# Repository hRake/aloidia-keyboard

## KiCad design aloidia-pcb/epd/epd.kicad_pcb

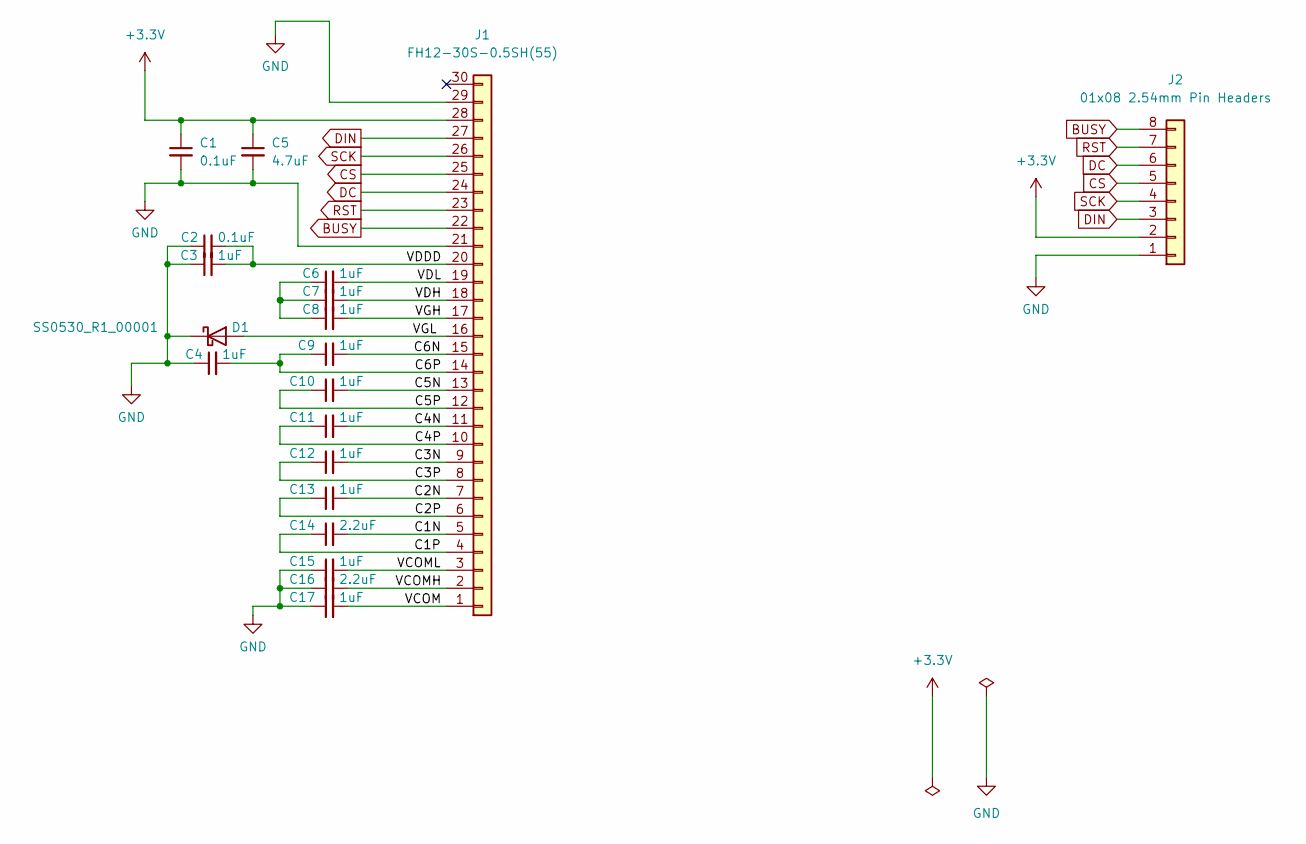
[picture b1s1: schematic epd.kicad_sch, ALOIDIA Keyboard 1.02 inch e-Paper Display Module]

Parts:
C1, C2: 0.1uF; C_0603_1608Metric
C3, C4, C6, C7, C8, C9, C10, C11, C12, C13, C15, C17: 1uF; C_0603_1608Metric
C5: 4.7uF; C_0603_1608Metric
C14, C16: 2.2uF; C_0603_1608Metric
D1: SS0530_R1_00001; D_SOD-123; Mouser ref 241-SS0530_R1_00001
J1: FH12-30S-0.5SH(55); JUSHUO AFC24-S30FIC-00; Mouser ref 798-FH12-30S-0.5SH55
J2: 01x08 2.54mm Pin Headers; PinHeader_1x08_P2.54mm_Vertical

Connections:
+3.3V: C1.1, C5.1, J1.28, J2.2
/C1N: C14.2, J1.5
/C1P: C14.1, J1.4
/C2N: C13.2, J1.7
/C2P: C13.1, J1.6
/C3N: C12.2, J1.9
/C3P: C12.1, J1.8
/C4N: C11.2, J1.11
/C4P: C11.1, J1.10
/C5N: C10.2, J1.13
/C5P: C10.1, J1.12
/C6N: C9.2, J1.15
/C6P: C4.2, C9.1, J1.14
/VCOM: C17.2, J1.1
/VCOMH: C16.2, J1.2
/VCOML: C15.2, J1.3
/VDDD: C2.2, C3.2, J1.20
/VDH: C7.2, J1.18
/VDL: C6.2, J1.19
/VGH: C8.2, J1.17
/VGL: D1.2 (A), J1.16
BUSY: J1.22, J2.8
CS: J1.25, J2.5
DC: J1.24, J2.6
DIN: J1.27, J2.3
GND: C1.2, C2.1, C3.1, C4.1, C5.2, C15.1, C16.1, C17.1, D1.1 (K), J1.21, J1.29, J2.1
unnamed: C6.1, C7.1, C8.1
RST: J1.23, J2.7
SCK: J1.26, J2.4

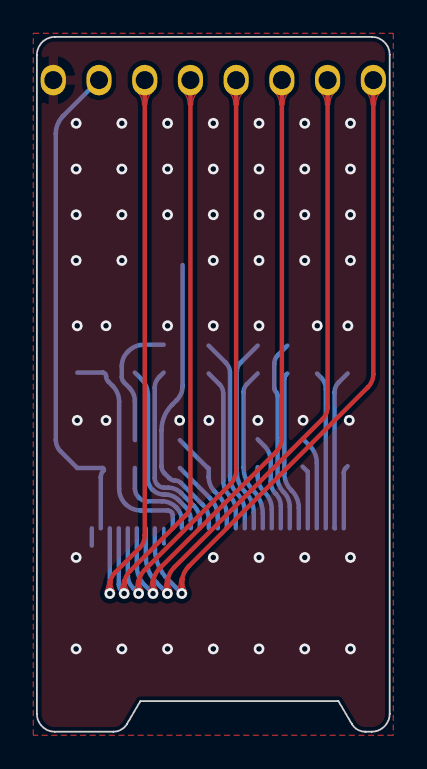
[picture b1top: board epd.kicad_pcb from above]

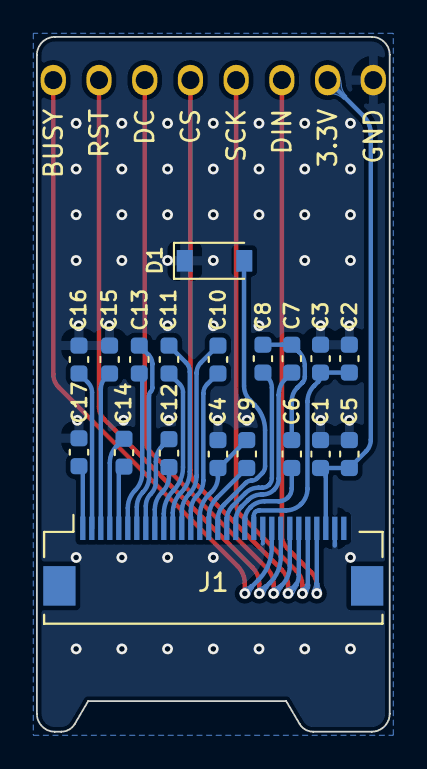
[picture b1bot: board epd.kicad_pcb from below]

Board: 2 copper layers, 19.6 x 38.6 mm, 20 parts (20 on the bottom side), 29 nets.

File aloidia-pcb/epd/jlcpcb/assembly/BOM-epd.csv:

Comment,Designator,Footprint,LCSC
0.1uF,"C1,C2",C_0603_1608Metric,C14663
1uF,"C10,C11,C12,C13,C15,C17,C3,C4,C6,C7,C8,C9",C_0603_1608Metric,C15849
4.7uF,C5,C_0603_1608Metric,C19666
2.2uF,"C14,C16",C_0603_1608Metric,C23630
FH12-30S-0.5SH(55),J1,JUSHUO AFC24-S30FIC-00,C262294
SS0530_R1_00001,D1,D_SOD-123,C8598

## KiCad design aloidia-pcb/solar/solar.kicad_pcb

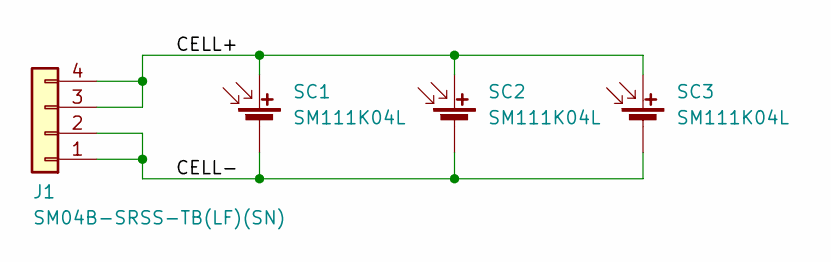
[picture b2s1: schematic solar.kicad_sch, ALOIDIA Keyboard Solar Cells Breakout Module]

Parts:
J1: SM04B-SRSS-TB(LF)(SN); JST_SH_SM04B-SRSS-TB_1x04-1MP_P1.00mm_Horizontal
SC1, SC2, SC3: SM111K04L; Digikey ref SM111K04L-ND

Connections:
/CELL+: J1.3, J1.4, SC1.1 (+), SC2.1 (+), SC3.1 (+)
/CELL-: J1.1, J1.2, SC1.2 (-), SC2.2 (-), SC3.2 (-)

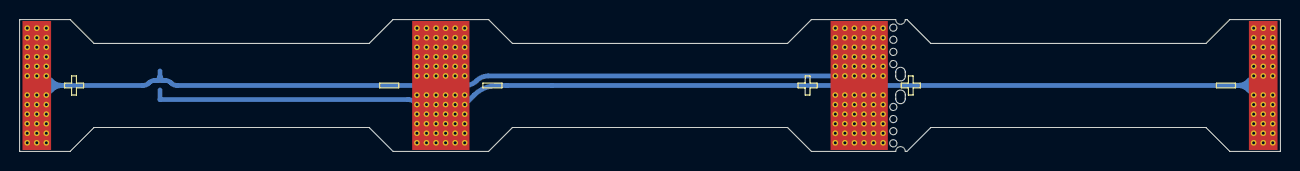
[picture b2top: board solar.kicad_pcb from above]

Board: 2 copper layers, 132.0 x 13.8 mm, 4 parts (1 on the bottom side), 2 nets.

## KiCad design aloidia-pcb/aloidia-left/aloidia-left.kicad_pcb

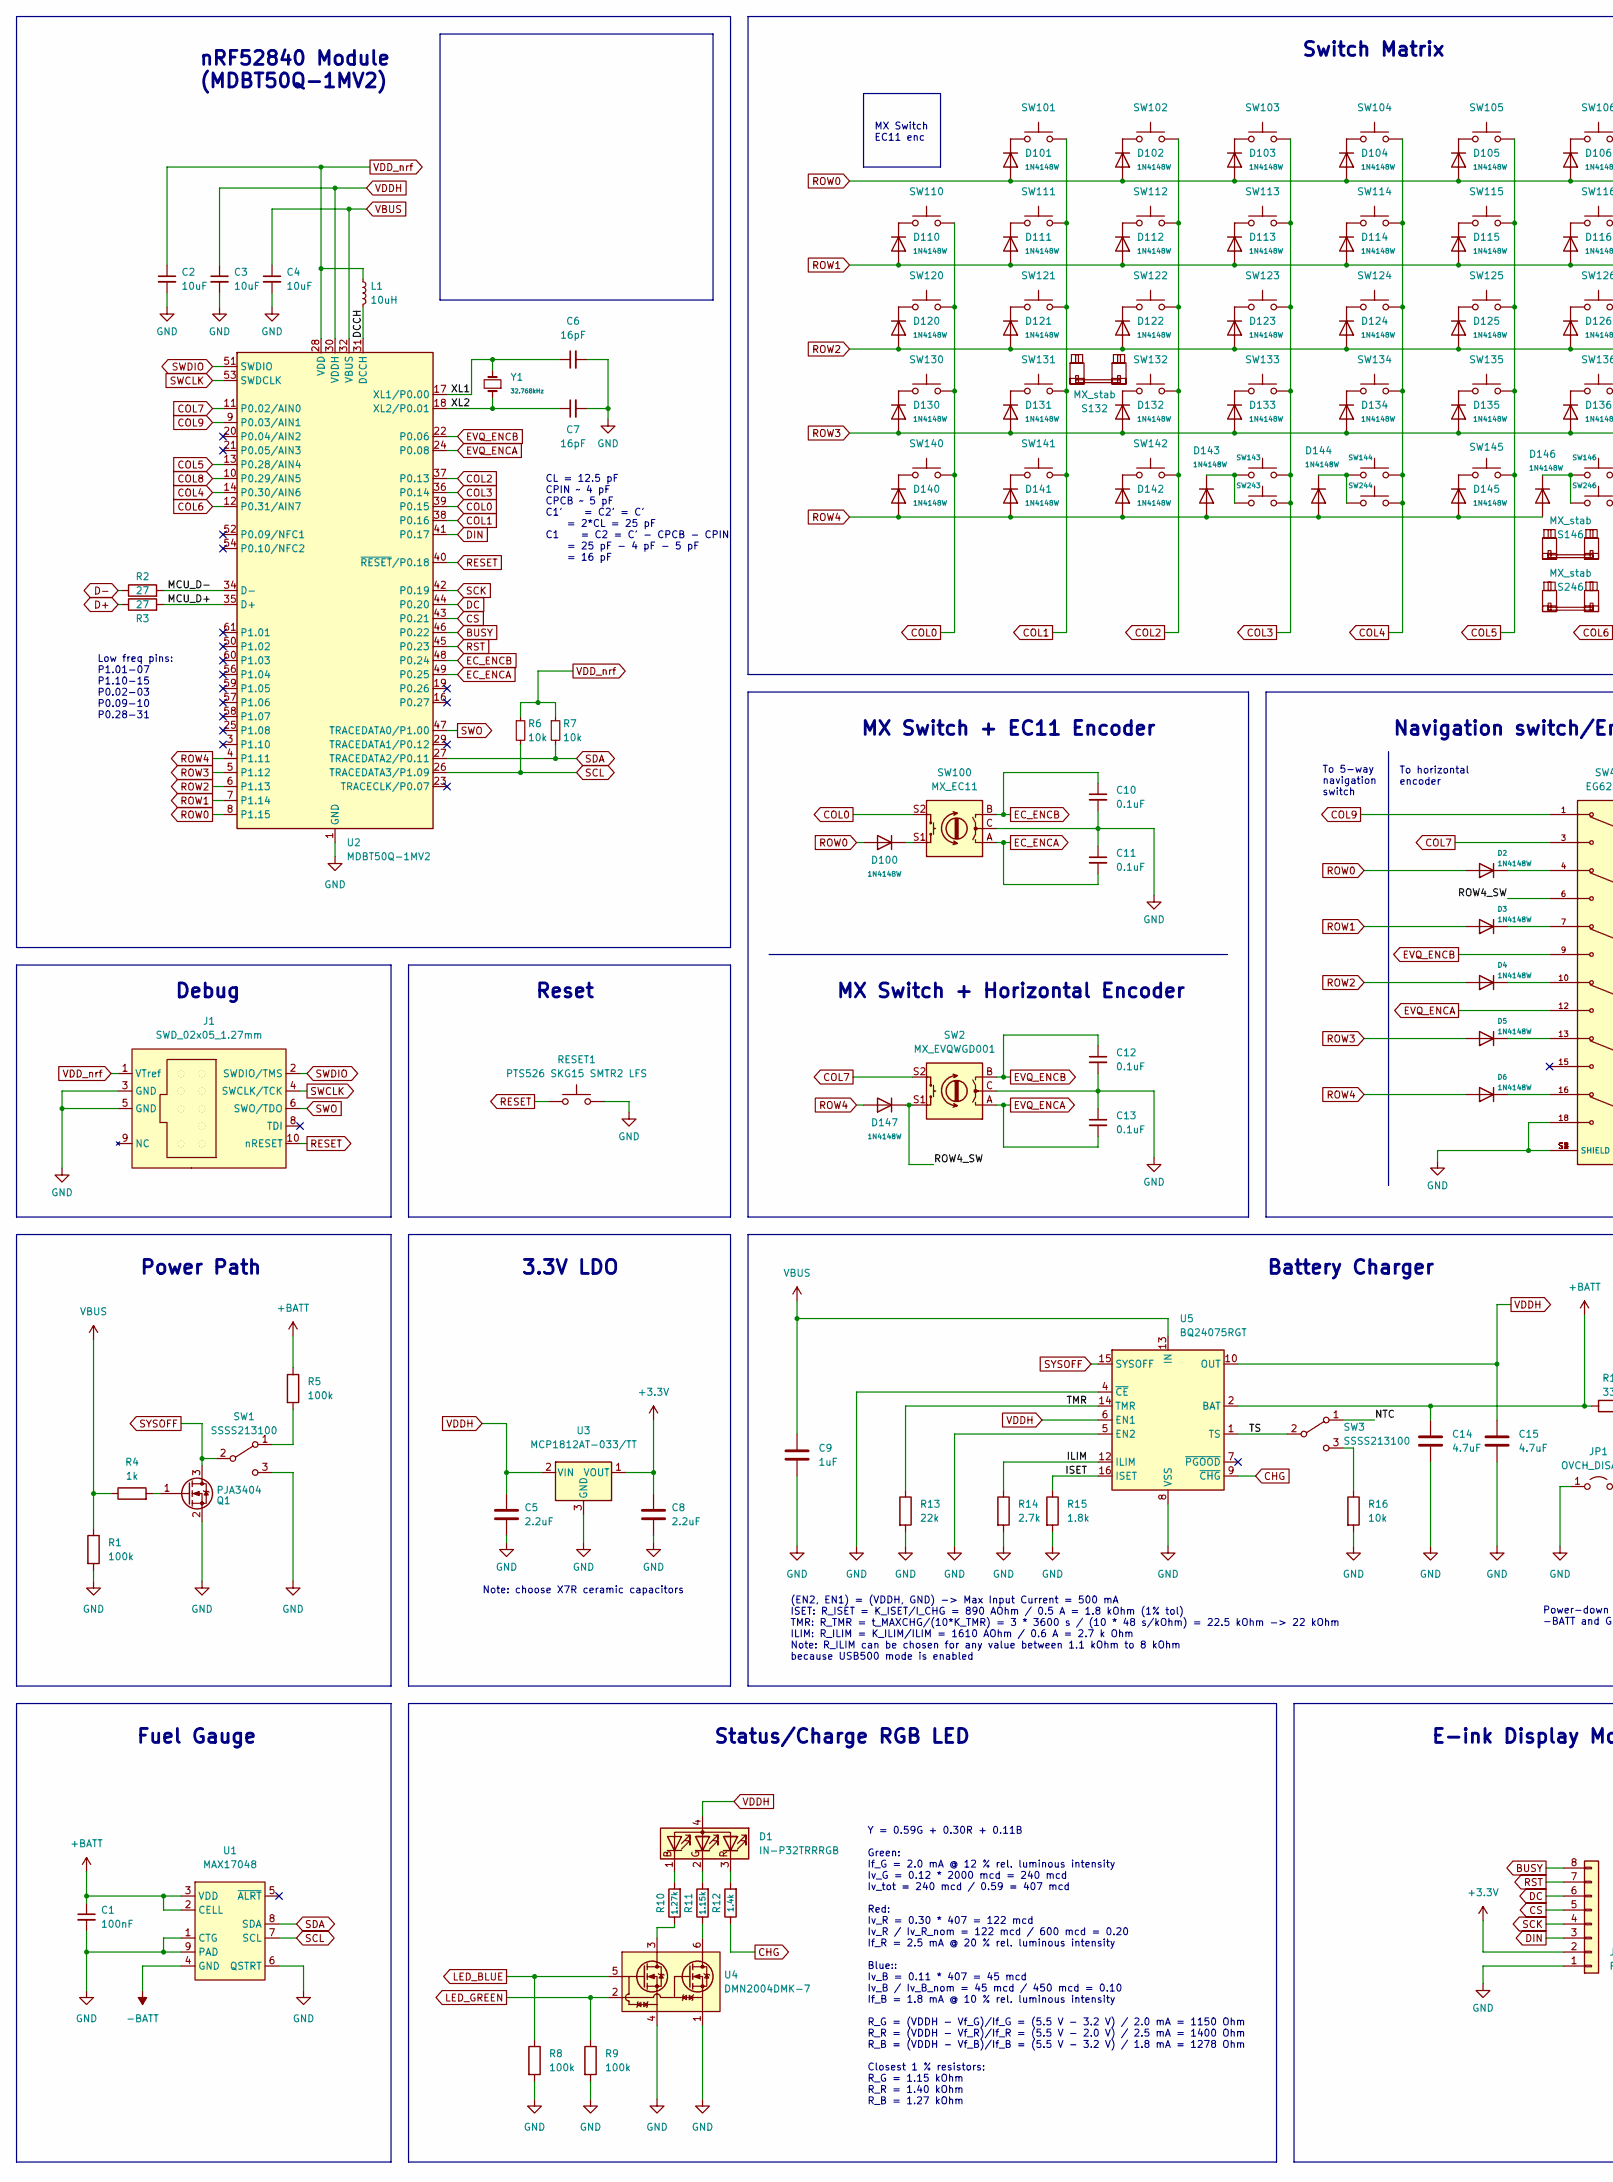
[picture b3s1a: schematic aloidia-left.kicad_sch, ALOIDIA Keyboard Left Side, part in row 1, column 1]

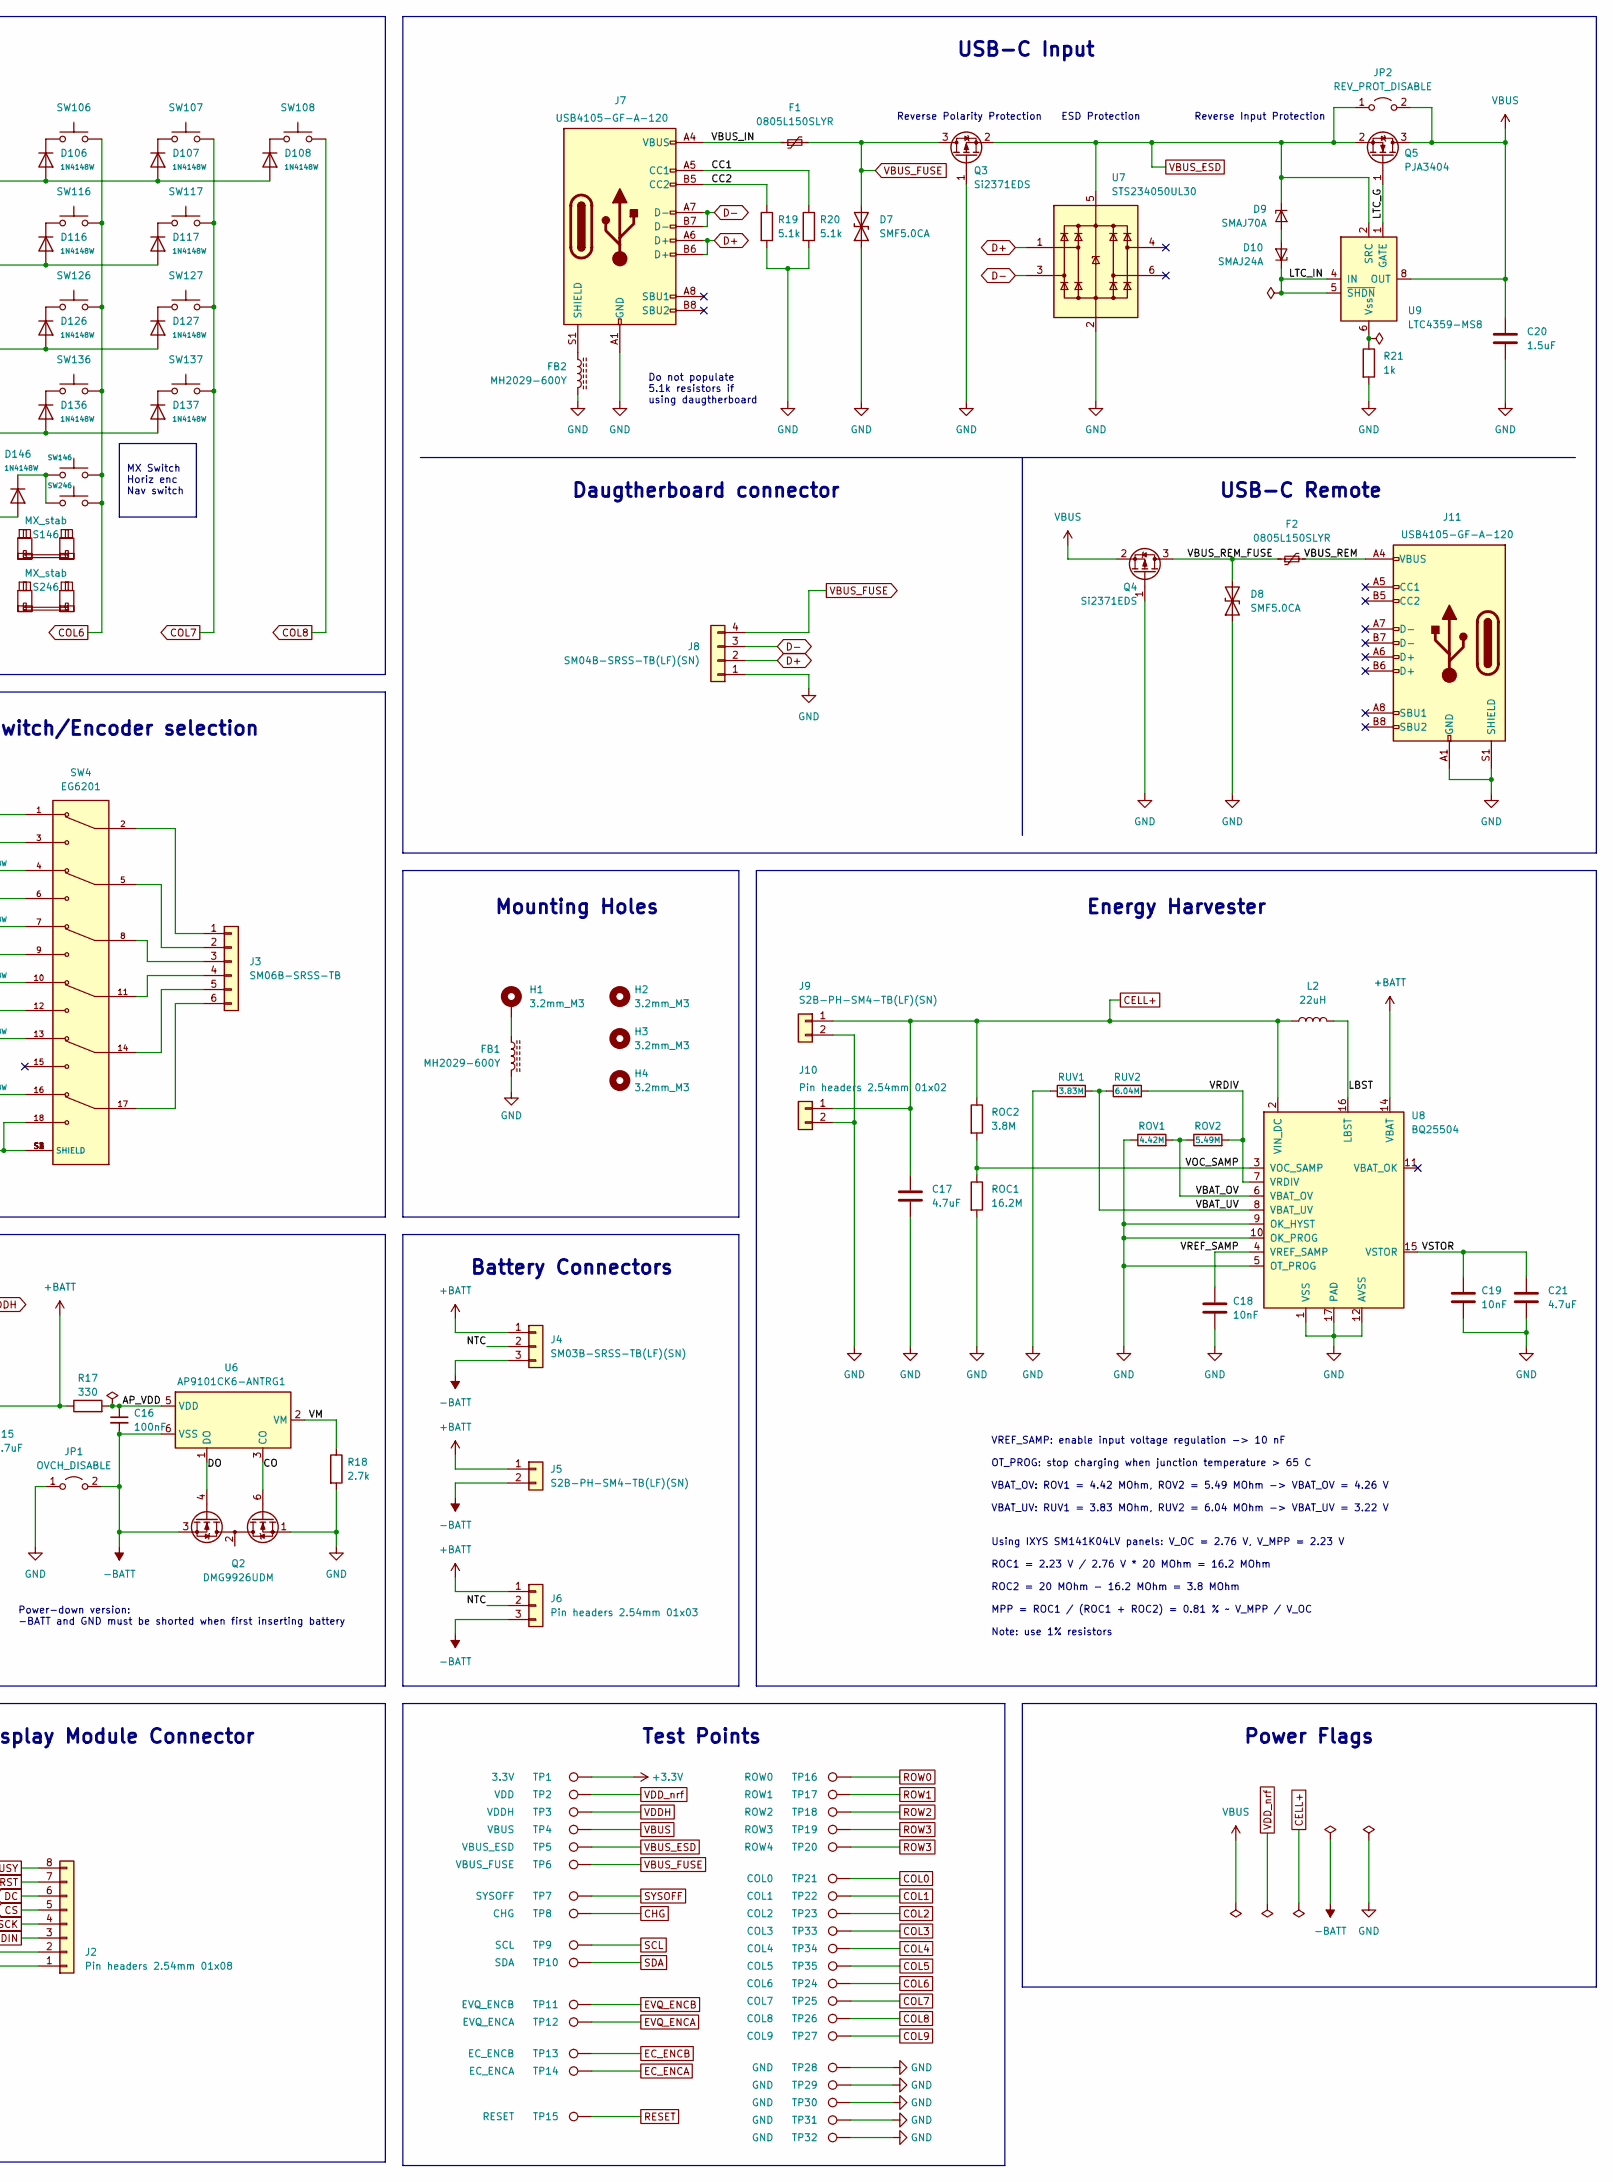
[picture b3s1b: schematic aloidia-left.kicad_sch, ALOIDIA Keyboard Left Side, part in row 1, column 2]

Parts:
C1, C16: 100nF; C_0603_1608Metric
C2, C3, C4: 10uF; C_0603_1608Metric
C5, C8: 2.2uF; C_0603_1608Metric
C6, C7: 16pF; C_0603_1608Metric
C9: 1uF; C_0603_1608Metric
C10, C11, C12, C13: 0.1uF; C_0603_1608Metric
C14, C15, C17, C21: 4.7uF; C_0603_1608Metric
C18, C19: 10nF; C_0603_1608Metric
C20: 1.5uF; C_0603_1608Metric
D1: IN-P32TRRRGB; Mouser ref 743-IN-P32TRRRGB
D2, D3, D4, D5, D6, D100, D101, D102, D103, D104, D105, D106, D107, D108, D110, D111, D112, D113, D114, D115, D116, D117, D120, D121, D122, D123, D124, D125, D126, D127, D130, D131, D132, D133, D134, D135, D136, D137, D140, D141, D142, D143, D144, D145, D146, D147: 1N4148W; D_SOD-123
D7, D8: SMF5.0CA; D_SOD-123; Mouser ref 576-SMF5.0CA
D9: SMAJ70A; D_SMA; Mouser ref 576-SMAJ24A
D10: SMAJ24A; D_SMA; Mouser ref 652-SMAJ70A
F1, F2: 0805L150SLYR; Fuse_0805_2012Metric; Mouser ref 576-0805L150SLYR
FB1, FB2: MH2029-600Y; L_0805_2012Metric
H1, H2, H3, H4: 3.2mm_M3; MountingHole_3.2mm_M3_Pad_Via
J1: SWD_02x05_1.27mm; FTSH-105-01; Mouser ref 485-4048
J2: Pin headers 2.54mm 01x08; PinHeader_1x08_P2.54mm_Vertical
J3: SM06B-SRSS-TB; JST_SH_SM06B-SRSS-TB_1x06-1MP_P1.00mm_Horizontal
J4: SM03B-SRSS-TB(LF)(SN); JST_SH_SM03B-SRSS-TB_1x03-1MP_P1.00mm_Horizontal
J5, J9: S2B-PH-SM4-TB(LF)(SN); JST_PH_S2B-PH-SM4-TB_1x02-1MP_P2.00mm_Horizontal
J6: Pin headers 2.54mm 01x03; PinSocket_1x03_P2.54mm_Vertical
J7, J11: USB4105-GF-A-120; USB_C_Receptacle_HRO_TYPE-C-31-M-12; Mouser ref 640-USB4105-GF-A-120
J8: SM04B-SRSS-TB(LF)(SN); JST_SH_SM04B-SRSS-TB_1x04-1MP_P1.00mm_Horizontal
J10: Pin headers 2.54mm 01x02; PinHeader_1x02_P2.54mm_Vertical
JP1: OVCH_DISABLE; SolderJumper-2_P1.3mm_Open_RoundedPad1.0x1.5mm
JP2: REV_PROT_DISABLE; SolderJumper-2_P1.3mm_Open_RoundedPad1.0x1.5mm
L1: 10uH; L_0603_1608Metric
L2: 22uH; L_0603_1608Metric
Q1, Q5: PJA3404; SOT-23; Mouser ref 241-PJA3404_R1_00001
Q2: DMG9926UDM; SOT-23-6; Mouser ref 621-DMG9926UDM-7
Q3, Q4: Si2371EDS; SOT-23; Mouser ref 78-SI2371EDS-T1-BE3
R1, R5, R8, R9: 100k; R_0603_1608Metric
R2, R3: 27; R_0603_1608Metric
R4, R21: 1k; R_0603_1608Metric
R6, R7, R16: 10k; R_0603_1608Metric
R10: 1.27k; R_0603_1608Metric
R11: 1.15k; R_0603_1608Metric
R12: 1.4k; R_0603_1608Metric
R13: 22k; R_0603_1608Metric
R14, R18: 2.7k; R_0603_1608Metric
R15: 1.8k; R_0603_1608Metric
R17: 330; R_0603_1608Metric
R19, R20: 5.1k; R_0603_1608Metric
RESET1: PTS526 SKG15 SMTR2 LFS; PTS526; Mouser ref 611-PTS526SKG15SMR2L
ROC1: 16.2M; R_0603_1608Metric
ROC2: 3.8M; R_0603_1608Metric
ROV1: 4.42M; R_0603_1608Metric
ROV2: 5.49M; R_0603_1608Metric
RUV1: 3.83M; R_0603_1608Metric
RUV2: 6.04M; R_0603_1608Metric
S132, S146: MX_stab; STAB_MX_P_2.25u
S246: MX_stab; STAB_MX_P_2.75u
SW1, SW3: SSSS213100; SW_SSSS213100; Mouser ref 688-SSSS213100
SW2: MX_EVQWGD001; MX_HS_AS_1u_EVQWGD001
SW4: EG6201; SW_EG6201; Mouser ref 612-EG6201
SW100: MX_EC11; MX_HS_AS_EC11_1u
SW101, SW102, SW103, SW104, SW105, SW106, SW107, SW108, SW110, SW111, SW113, SW114, SW115, SW116, SW117, SW120, SW121, SW123, SW124, SW125, SW126, SW127, SW130, SW131, SW132, SW133, SW134, SW135, SW136, SW137, SW140, SW141, SW145, SW146, SW243, SW246: SW_Push; MX_HS_AS_1u
SW112, SW144: SW_Push; MX_HS_AS_1.5u
SW122: SW_Push; MX_HS_AS_1.75u
SW142, SW143, SW244: SW_Push; MX_HS_AS_1.25u
TP1: 3.3V; TestPoint
TP2: VDD; TestPoint
TP3: VDDH; TestPoint
TP4: VBUS; TestPoint
TP5: VBUS_ESD; TestPoint
TP6: VBUS_FUSE; TestPoint
TP7: SYSOFF; TestPoint
TP8: CHG; TestPoint
TP9: SCL; TestPoint
TP10: SDA; TestPoint
TP11: EVQ_ENCB; TestPoint
TP12: EVQ_ENCA; TestPoint
TP13: EC_ENCB; TestPoint
TP14: EC_ENCA; TestPoint
TP15: RESET; TestPoint
TP16: ROW0; TestPoint
TP17: ROW1; TestPoint
TP18: ROW2; TestPoint
TP19: ROW3; TestPoint
TP20: ROW4; TestPoint
TP21: COL0; TestPoint
TP22: COL1; TestPoint
TP23: COL2; TestPoint
TP24: COL6; TestPoint
TP25: COL7; TestPoint
TP26: COL8; TestPoint
TP27: COL9; TestPoint
TP28, TP29, TP30, TP31, TP32: GND; TestPoint
TP33: COL3; TestPoint
TP34: COL4; TestPoint
TP35: COL5; TestPoint
U1: MAX17048; TDFN-8-1EP_2x2mm_P0.5mm_EP0.8x1.2mm; Mouser ref 700-MAX17048G+T10
U2: MDBT50Q-1MV2; Raytac_MDBT50Q
U3: MCP1812AT-033/TT; SOT-23; Mouser ref 579-MCP1812AT-033/TT
U4: DMN2004DMK-7; SOT-23-6; Digikey ref DMN2004DMKDICT-ND
U5: BQ24075RGT; VQFN-16-1EP_3x3mm_P0.5mm_EP1.6x1.6mm; Mouser ref 595-BQ24075RGTR
U6: AP9101CK6-ANTRG1; SOT-23-6; Digikey ref AP9101CK6-ANTRG1DICT-ND
U7: STS234050UL30; SOT-23-6; Mouser ref 504-STS234050UL30
U8: BQ25504; VQFN-16-1EP_3x3mm_P0.5mm_EP1.6x1.6mm; Mouser ref 595-BQ25504RGTR
U9: LTC4359-MS8; MSOP-8_3x3mm_P0.65mm
Y1: 32.768kHz; Crystal_SMD_MicroCrystal_CM9V-T1A-2Pin_1.6x1.0mm

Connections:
+3.3V: C8.1, J2.2, TP1.1, U3.1 (VOUT)
+BATT: C1.1, C14.1, J4.1, J5.1, J6.1, R5.1, R17.1, U1.2 (CELL), U1.3 (VDD), U5.2 (BAT), U5.3 (BAT), U8.14 (VBAT)
-BATT: C16.2, J4.3, J5.2, J6.3, JP1.2 (B), Q2.3 (S2), U1.4 (GND), U6.6 (VSS)
/AP_VDD: C16.1, R17.2, U6.5 (VDD)
/CC1: J7.A5 (CC1), R20.1
/CC2: J7.B5 (CC2), R19.1
/CO: Q2.6 (G1), U6.3 (CO)
/DCCH: L1.2, U2.31 (DCCH)
/DO: Q2.4 (G2), U6.1 (DO)
/ILIM: R14.1, U5.12 (ILIM)
/ISET: R15.1, U5.16 (ISET)
/LBST: L2.2, U8.16 (LBST)
/LTC_G: Q5.1 (G), U9.1 (GATE)
/LTC_IN: D10.1 (K1), U9.4 (IN), U9.5 (~SHDN)
/MCU_D+: R3.2, U2.35 (D+)
/MCU_D-: R2.2, U2.34 (D-)
/NTC: J4.2, J6.2, SW3.1 (A)
/ROW4_SW: D147.1 (K), SW2.S1, SW4.6
/TMR: R13.1, U5.14 (TMR)
/TS: SW3.2 (B), U5.1 (TS)
/VBAT_OV: ROV1.2, ROV2.1, U8.6 (VBAT_OV)
/VBAT_UV: RUV1.2, RUV2.1, U8.8 (VBAT_UV)
/VBUS_IN: F1.1, J7.A4 (VBUS), J7.A9 (VBUS), J7.B4 (VBUS), J7.B9 (VBUS)
/VBUS_REM: F2.2, J11.A4 (VBUS), J11.A9 (VBUS), J11.B4 (VBUS), J11.B9 (VBUS)
/VBUS_REM_FUSE: D8.2 (A2), F2.1, Q4.3 (D)
/VM: R18.1, U6.2 (VM)
/VOC_SAMP: ROC1.1, ROC2.2, U8.3 (VOC_SAMP)
/VRDIV: ROV2.2, RUV2.2, U8.7 (VRDIV)
/VREF_SAMP: C18.1, U8.4 (VREF_SAMP)
/VSTOR: C19.1, C21.1, U8.15 (VSTOR)
/XL1: C6.1, U2.17 (XL1/P0.00), Y1.2
/XL2: C7.1, U2.18 (XL2/P0.01), Y1.1
BUSY: J2.8, U2.46 (P0.22)
CELL+: C17.1, J9.1, J10.1, L2.1, ROC2.1, U8.2 (VIN_DC)
CHG: R12.1, TP8.1, U5.9 (~CHG)
COL0: SW100.S2, SW110.2, SW120.2, SW130.2, SW140.2, TP21.1, U2.39 (P0.15)
COL1: SW101.2, SW111.2, SW121.2, SW131.2, SW141.2, TP22.1, U2.38 (P0.16)
COL2: SW102.2, SW112.2, SW122.2, SW132.2, SW142.2, TP23.1, U2.37 (P0.13)
COL3: SW103.2, SW113.2, SW123.2, SW133.2, SW143.2, SW243.2, TP33.1, U2.36 (P0.14)
COL4: SW104.2, SW114.2, SW124.2, SW134.2, SW144.2, SW244.2, TP34.1, U2.14 (P0.30/AIN6)
COL5: SW105.2, SW115.2, SW125.2, SW135.2, SW145.2, TP35.1, U2.13 (P0.28/AIN4)
COL6: SW106.2, SW116.2, SW126.2, SW136.2, SW146.2, SW246.2, TP24.1, U2.12 (P0.31/AIN7)
COL7: SW2.S2, SW4.3, SW107.2, SW117.2, SW127.2, SW137.2, TP25.1, U2.11 (P0.02/AIN0)
COL8: SW108.2, TP26.1, U2.10 (P0.29/AIN5)
COL9: SW4.1, TP27.1, U2.9 (P0.03/AIN1)
CS: J2.5, U2.43 (P0.21)
D+: J7.A6 (D+), J7.B6 (D+), J8.2, R3.1, U7.1 (IO1)
D-: J7.A7 (D-), J7.B7 (D-), J8.3, R2.1, U7.3 (IO2)
DC: J2.6, U2.44 (P0.20)
DIN: J2.3, U2.41 (P0.17)
EC_ENCA: C11.2, SW100.A, TP14.1, U2.49 (P0.25)
EC_ENCB: C10.1, SW100.B, TP13.1, U2.48 (P0.24)
EVQ_ENCA: C13.2, SW2.A, SW4.12, TP12.1, U2.24 (P0.08)
EVQ_ENCB: C12.1, SW2.B, SW4.9, TP11.1, U2.22 (P0.06)
GND: C1.2, C2.2, C3.2, C4.2, C5.2, C6.2, C7.2, C8.2, C9.2, C10.2, C11.1, C12.2, C13.1, C14.2, C15.2, C17.2, C18.2, C19.2, C20.2, C21.2, D7.1 (A1), D8.1 (A1), FB1.2, FB2.2, J1.3 (GND), J1.5 (GND), J2.1, J7.A1 (GND), J7.A12 (GND), J7.B1 (GND), J7.B12 (GND), J8.1, J9.2, J10.2, J11.A1 (GND), J11.A12 (GND), J11.B1 (GND), J11.B12 (GND), J11.S1 (SHIELD), JP1.1 (A), Q1.2 (S), Q2.1 (D1), Q3.1 (G), Q4.1 (G), R1.2, R8.2, R9.2, R13.2, R14.2, R15.2, R16.2, R18.2, R19.2, R20.2, R21.2, RESET1.2, ROC1.2, ROV1.1, RUV1.1, SW1.3 (C), SW2.C, SW4.18, SW4.S1 (SHIELD), SW4.S2 (SHIELD), SW4.S3 (SHIELD), SW4.S4 (SHIELD), SW100.C, TP28.1, TP29.1, TP30.1, TP31.1, TP32.1, U1.1 (CTG), U1.6 (QSTRT), U1.9 (PAD), U2.1 (GND), U2.2 (GND), U2.15 (GND), U2.33 (GND), U2.55 (GND), U3.3 (GND), U4.1 (S2), U4.4 (S1), U5.4 (~CE), U5.5 (EN2), U5.8 (VSS), U5.17 (VSS), U7.2 (VN), U8.1 (VSS), U8.5 (OT_PROG), U8.9 (OK_HYST), U8.10 (OK_PROG), U8.12 (AVSS), U8.13 (VSS), U8.17 (PAD)
LED_BLUE: R8.1, U4.5 (G1)
LED_GREEN: R9.1, U4.2 (G2)
unnamed: D1.1 (BK), R10.2
unnamed: D1.2 (GK), R11.2
unnamed: D1.3 (RK), R12.2
unnamed: D2.1 (K), SW4.4
unnamed: D3.1 (K), SW4.7
unnamed: D4.1 (K), SW4.10
unnamed: D5.1 (K), SW4.13
unnamed: D6.1 (K), SW4.16
unnamed: D9.2 (A), D10.2 (A)
unnamed: D100.1 (K), SW100.S1
unnamed: D101.1 (K), SW101.1
unnamed: D102.1 (K), SW102.1
unnamed: D103.1 (K), SW103.1
unnamed: D104.1 (K), SW104.1
unnamed: D105.1 (K), SW105.1
unnamed: D106.1 (K), SW106.1
unnamed: D107.1 (K), SW107.1
unnamed: D108.1 (K), SW108.1
unnamed: D110.1 (K), SW110.1
unnamed: D111.1 (K), SW111.1
unnamed: D112.1 (K), SW112.1
unnamed: D113.1 (K), SW113.1
unnamed: D114.1 (K), SW114.1
unnamed: D115.1 (K), SW115.1
unnamed: D116.1 (K), SW116.1
unnamed: D117.1 (K), SW117.1
unnamed: D120.1 (K), SW120.1
unnamed: D121.1 (K), SW121.1
unnamed: D122.1 (K), SW122.1
unnamed: D123.1 (K), SW123.1
unnamed: D124.1 (K), SW124.1
unnamed: D125.1 (K), SW125.1
unnamed: D126.1 (K), SW126.1
unnamed: D127.1 (K), SW127.1
unnamed: D130.1 (K), SW130.1
unnamed: D131.1 (K), SW131.1
unnamed: D132.1 (K), SW132.1
unnamed: D133.1 (K), SW133.1
unnamed: D134.1 (K), SW134.1
unnamed: D135.1 (K), SW135.1
unnamed: D136.1 (K), SW136.1
unnamed: D137.1 (K), SW137.1
unnamed: D140.1 (K), SW140.1
unnamed: D141.1 (K), SW141.1
unnamed: D142.1 (K), SW142.1
unnamed: D143.1 (K), SW143.1, SW243.1
unnamed: D144.1 (K), SW144.1, SW244.1
unnamed: D145.1 (K), SW145.1
unnamed: D146.1 (K), SW146.1, SW246.1
unnamed: FB1.1, H1.1
unnamed: FB2.1, J7.S1 (SHIELD)
unnamed: J3.1, SW4.2
unnamed: J3.2, SW4.5
unnamed: J3.3, SW4.8
unnamed: J3.4, SW4.11
unnamed: J3.5, SW4.14
unnamed: J3.6, SW4.17
unnamed: Q1.1 (G), R4.2
unnamed: Q2.2 (S1/D2), Q2.5 (S1/D2)
unnamed: R5.2, SW1.1 (A)
unnamed: R10.1, U4.3 (D1)
unnamed: R11.1, U4.6 (D2)
unnamed: R16.1, SW3.3 (C)
unnamed: R21.1, U9.6 (Vss)
RESET: J1.10 (nRESET), RESET1.1, TP15.1, U2.40 (~RESET/P0.18)
ROW0: D2.2 (A), D100.2 (A), D101.2 (A), D102.2 (A), D103.2 (A), D104.2 (A), D105.2 (A), D106.2 (A), D107.2 (A), D108.2 (A), TP16.1, U2.8 (P1.15)
ROW1: D3.2 (A), D110.2 (A), D111.2 (A), D112.2 (A), D113.2 (A), D114.2 (A), D115.2 (A), D116.2 (A), D117.2 (A), TP17.1, U2.7 (P1.14)
ROW2: D4.2 (A), D120.2 (A), D121.2 (A), D122.2 (A), D123.2 (A), D124.2 (A), D125.2 (A), D126.2 (A), D127.2 (A), TP18.1, U2.6 (P1.13)
ROW3: D5.2 (A), D130.2 (A), D131.2 (A), D132.2 (A), D133.2 (A), D134.2 (A), D135.2 (A), D136.2 (A), D137.2 (A), TP19.1, TP20.1, U2.5 (P1.12)
ROW4: D6.2 (A), D140.2 (A), D141.2 (A), D142.2 (A), D143.2 (A), D144.2 (A), D145.2 (A), D146.2 (A), D147.2 (A), U2.4 (P1.11)
RST: J2.7, U2.45 (P0.23)
SCK: J2.4, U2.42 (P0.19)
SCL: R6.2, TP9.1, U1.7 (SCL), U2.26 (TRACEDATA3/P1.09)
SDA: R7.2, TP10.1, U1.8 (SDA), U2.27 (TRACEDATA2/P0.11)
SWCLK: J1.4 (SWCLK/TCK), U2.53 (SWDCLK)
SWDIO: J1.2 (SWDIO/TMS), U2.51 (SWDIO)
SWO: J1.6 (SWO/TDO), U2.47 (TRACEDATA0/P1.00)
SYSOFF: Q1.3 (D), SW1.2 (B), TP7.1, U5.15 (SYSOFF)
VBUS: C4.1, C9.1, C20.1, JP2.2 (B), Q4.2 (S), Q5.3 (D), R1.1, R4.1, TP4.1, U2.32 (VBUS), U5.13 (IN), U9.8 (OUT)
VBUS_ESD: D9.1 (K1), JP2.1 (A), Q3.2 (S), Q5.2 (S), TP5.1, U7.5 (VP), U9.2 (SRC)
VBUS_FUSE: D7.2 (A2), F1.2, J8.4, Q3.3 (D), TP6.1
VDDH: C3.1, C5.1, C15.1, D1.4 (A), TP3.1, U2.30 (VDDH), U3.2 (VIN), U5.6 (EN1), U5.10 (OUT), U5.11 (OUT)
VDD_nrf: C2.1, J1.1 (VTref), L1.1, R6.1, R7.1, TP2.1, U2.28 (VDD)

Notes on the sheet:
MX Switch EC11 enc
Reverse Polarity Protection
nRF52840 Module (MDBT50Q-1MV2)
Switch Matrix
To horizontal encoder
Reverse Input Protection
CL = 12.5 pF CPIN ~ 4 pF CPCB ~ 5 pF C1' = C2' = C' = 2*CL = 25 pF C1 = C2 = C' - CPCB - CPIN = 25 pF - 4 pF - 5 pF = 16 pF
Mounting Holes
ESD Protection
(EN2, EN1) = (VDDH, GND) -> Max Input Current = 500 mA ISET: R_ISET = K_ISET/I_CHG = 890 AOhm / 0.5 A = 1.8 kOhm (1% tol) TMR: R_TMR = t_MAXCHG/(10*K_TMR) = 3 * 3600 s / (10 * 48 s/kOhm) = 22.5 kOhm -> 22 kOhm ILIM: R_ILIM = K_ILIM/ILIM = 1610 AOhm / 0.6 A = 2.7 k Ohm Note: R_ILIM can be chosen for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
Power Flags
MX Switch + Horizontal Encoder
Power-down version: -BATT and GND must be shorted when first inserting battery
Energy Harvester
MX Switch + EC11 Encoder
MX Switch Horiz enc Nav switch
Navigation switch/Encoder selection
Daugtherboard connector
VREF_SAMP: enable input voltage regulation -> 10 nF OT_PROG: stop charging when junction temperature > 65 C VBAT_OV: ROV1 = 4.42 MOhm, ROV2 = 5.49 MOhm -> VBAT_OV = 4.26 V VBAT_UV: RUV1 = 3.83 MOhm, RUV2 = 6.04 MOhm -> VBAT_UV = 3.22 V Using IXYS SM141K04LV panels: V_OC = 2.76 V, V_MPP = 2.23 V ROC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
To 5-way navigation switch
Low freq pins: P1.01-07 P1.10-15 P0.02-03 P0.09-10 P0.28-31
Debug
Reset
USB-C Input
Fuel Gauge
Battery Connectors
Test Points
Battery Charger
Power Path
E-ink Display Module Connector
Y = 0.59G + 0.30R + 0.11B Green: If_G = 2.0 mA @ 12 % rel. luminous intensity Iv_G = 0.12 * 2000 mcd = 240 mcd Iv_tot = 240 mcd / 0.59 = 407 mcd Red: Iv_R = 0.30 * 407 = 122 mcd Iv_R / Iv_R_nom = 122 mcd / 600 mcd = 0.20 If_R = 2.5 mA @ 20 % rel. luminous intensity Blue:: Iv_B = 0.11 * 407 = 45 mcd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
Do not populate 5.1k resistors if using daugtherboard
3.3V LDO
USB-C Remote
Note: choose X7R ceramic capacitors
Status/Charge RGB LED

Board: 2 copper layers, 223 parts (0 on the bottom side), 140 nets, no tracks yet.

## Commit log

2022-07-06 Finished schematics of left half
2022-07-06 Assigned all footprints
2022-07-06 Added design rules, net classes constraints and all footprint 3d models
2022-07-09 Routed left side
2022-07-10 Added production files for e-paper display module
2022-07-10 Changed page settings
2022-07-10 Added pin legends
2022-07-10 Fixed user comments alignment and metadata
2022-07-10 Fixed text labels orientation
2022-07-10 Added e-Paper display mechanical footprint
2022-07-10 Added round tracks config file to .gitignore
2022-07-10 Added solar cells breakout module
2022-07-10 Added solar breakout module outline dimensions
2022-07-10 Locked mousebites
2022-07-10 Added connector 3d model
2022-07-10 Added solar breakout module physical footprint
2022-07-10 Moved diode up
2022-07-10 Extended mcu ground keepout zone
2022-07-10 Changed silkscreen text size
2022-07-12 Changed connectors to jst-sh
2022-07-14 Adjusted trace widths
2022-07-14 FInished routing right side
2022-07-14 Added 1mm mousebite footprints
2022-07-14 Rectified stackup colors
2022-07-14 Fixed via
2022-07-14 Added unconnected symbols
2022-07-14 Added 3d model for U1
